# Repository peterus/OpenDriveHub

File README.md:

# OpenDriveHub

Open-source modular control platform for functional model vehicles (excavators,
dump trucks, tractors, and other ground-based RC models).

## Features

- **Modular transmitter** – plug-in front-panel slots for switches, buttons,
  potentiometers, and encoders; detected automatically at boot
- **I²C backplane** with TCA9548A multiplexer – identical standard I²C devices
  in every slot, no address conflicts, no MCU needed on modules
- **Always-on bidirectional telemetry** – battery voltage, RSSI, link state,
  and custom sensor values returned from the model
- **ESP32-based** firmware using PlatformIO + Arduino + FreeRTOS
- **Modern C++20** – `namespace odh`, `enum class`, `constexpr`, `std::optional`,
  RAII wrappers, shared libraries
- **ESP-NOW radio link** – low-latency, no router required
- **ILI9341 touch-screen display** – 320×240 colour LCD with XPT2046 resistive
  touch, LVGL widget UI for vehicle selection and live channel monitoring
- **PCA9685 servo driver** – I²C-based 16-channel PWM output on the receiver
- **Receiver-initiated discovery** – receivers broadcast their presence;
  the operator selects a vehicle on the transmitter touch screen
- **Vehicle model presets** – built-in function-to-channel maps for Generic,
  Dump Truck, Excavator, Tractor, and Crane models
- **Always-on web configuration** – WiFi AP + REST API (ESPAsyncWebServer +
  ArduinoJson v7) on both transmitter and receiver; starts automatically at
  boot, no button required; settings stored in ESP32 NVS
- **Linux simulation** – full transmitter + receiver simulation on a PC; SDL2
  display window, keyboard channel control, UDP radio loopback
- **Open hardware + firmware** under GPL-3.0

## Repository Structure

```
OpenDriveHub/
├── firmware/                   # Unified PlatformIO project (C++20, namespace odh::)
│   ├── platformio.ini          # Build config for all 5 environments
│   ├── lib/                    # Shared libraries
│   │   ├── odh-protocol/      # Packet definitions & function mapping
│   │   ├── odh-config/        # Compile-time configuration & NVS store
│   │   ├── odh-radio/         # ESP-NOW radio link (TX + RX)
│   │   ├── odh-telemetry/     # Battery monitor & telemetry data
│   │   └── odh-web/           # ESPAsyncWebServer + REST API helpers
│   ├── src/
│   │   ├── receiver/          # Receiver app (OutputManager, PCA9685, ReceiverApi)
│   │   └── transmitter/       # Transmitter app (Modules, Display, TransmitterApi)
│   ├── test/test_native/      # Native unit tests (90 tests, no hardware needed)
│   ├── data/                   # LittleFS web UI (receiver/ and transmitter/)
│   ├── include/                # LVGL & TFT_eSPI build-config headers
│   └── sim/                    # Linux simulation shims (SDL2, UDP, pthreads)
│       ├── include/            # Replacement headers (Arduino.h, esp_now.h, …)
│       └── src/                # Shim implementations
├── hardware/
│   ├── transmitter/            # Transmitter BOM and wiring reference
│   ├── receiver/               # Receiver BOM and wiring reference
│   └── modules/                # Per-module hardware documentation
│       ├── switch/
│       ├── button/
│       ├── potentiometer/
│       └── encoder/
└── docs/
    ├── index.md                # GitHub Pages one-pager
    ├── getting-started.md
    ├── architecture.md
    ├── backplane.md
    └── protocol.md
```

## Quick Start

See **[docs/getting-started.md](docs/getting-started.md)** for full build and
flash instructions.

```bash
cd firmware

# Flash transmitter
pio run -e transmitter -t upload

# Flash receiver
pio run -e receiver -t upload

# Run host-side unit tests (90 tests)
pio test -e native
```

### Run the simulation (no hardware needed)

```bash
cd firmware

# Terminal 1 – receiver
pio run -e sim_rx -t exec

# Terminal 2 – transmitter (headless terminal simulation)
pio run -e sim_tx -t exec
```

See **[firmware/sim/README.md](firmware/sim/README.md)** for full simulation docs.

## Supported Module Types

| Module | I²C Device | Channels |
|--------|------------|----------|
| Switch (toggle) | PCF8574 @ 0x20 | 8 |
| Button (momentary) | PCF8574 @ 0x21 | 8 |
| Potentiometer / fader | ADS1115 @ 0x48 | 4 |
| Encoder (absolute) | AS5600 @ 0x36 | 1 |

## Documentation

- [Getting Started](docs/getting-started.md)
- [System Architecture](docs/architecture.md)
- [Backplane & Modules](docs/backplane.md)
- [Radio Protocol](docs/protocol.md)
- [Transmitter Hardware](hardware/transmitter/README.md)
- [Receiver Hardware](hardware/receiver/README.md)
- [Simulation](firmware/sim/README.md)

## License

GPL-3.0 – see [LICENSE](LICENSE).

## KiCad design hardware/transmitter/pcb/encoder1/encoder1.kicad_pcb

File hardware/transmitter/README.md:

# Transmitter Hardware

The OpenDriveHub transmitter is a hand-held controller built around an
**ESP32** development board.

---

## Block Diagram

```
                  ┌─────────────────────┐
         I²C     │    ESP32-DevKitC     │  SPI
  ┌──────────────┤ SDA=21  SCL=22      ├────────────┐
  │              │                      │            │
  │              │ GPIO34 (ADC) ← Batt  │    ┌───────┴───────┐
  │              │                      │    │  ILI9341 LCD  │
  │              │ MOSI=23 MISO=19      │    │  320×240      │
  │              │ SCK=18  CS=5         │    │  + XPT2046    │
  │              │ DC=27   RST=26       │    │    Touch      │
  │              │ BL=32   T_CS=4       │    └───────────────┘
  │              │ T_IRQ=33             │
  │              └─────────────────────┘
  │
  ├── TCA9548A (0x70)
  │     ├── CH0 → Slot 0
  │     ├── CH1 → Slot 1
  │     ├── …
  │     └── CH5 → Slot 5
  │
  └── (pull-ups 4k7 to 3V3)
```

---

## Bill of Materials

| Qty | Component | Notes |
|-----|-----------|-------|
| 1 | ESP32-DevKitC (or equivalent) | 38-pin recommended |
| 1 | ILI9341 SPI LCD 320×240 | 2.4″ or 2.8″ breakout |
| 1 | XPT2046 resistive touch controller | Usually integrated on LCD board |
| 1 | TCA9548A I²C multiplexer breakout | Adafruit 2717 or generic |
| 2 | 4.7 kΩ resistors | I²C pull-ups on SDA / SCL |
| 1 | Voltage divider (100 kΩ + 33 kΩ) | Battery ADC on GPIO34 |
| 1 | 2S LiPo battery (7.4 V) | Optional – can be USB-powered |
| 6 | 4-pin headers / connectors | Module slot connectors |

---

## GPIO Pinout

### SPI Display (ILI9341)

| GPIO | Function |
|------|----------|
| 23 | MOSI (SDI) |
| 19 | MISO (SDO) |
| 18 | SCK |
| 5 | CS (chip select) |
| 27 | DC (data / command) |
| 26 | RST (reset) |
| 32 | Backlight (active high) |

### Touch (XPT2046)

| GPIO | Function |
|------|----------|
| 4 | T_CS (touch chip select) |
| 33 | T_IRQ (touch interrupt) |

SPI bus is shared between LCD and touch.

### I²C Bus

| GPIO | Function |
|------|----------|
| 21 | SDA |
| 22 | SCL |

All modules and the TCA9548A mux share this bus at 400 kHz.

### Battery ADC

| GPIO | Function |
|------|----------|
| 34 | Battery voltage via divider |

Divider ratio: `odh::config::kBatteryDividerRatio` (default 4.03).

---

## Programming

```bash
cd firmware
pio run -e transmitter -t upload
pio run -e transmitter -t monitor   # 115200 baud
```

---

## WiFi Configuration

The transmitter starts a WiFi AP automatically at every boot:

- **SSID:** `OpenDriveHub-Config` (configurable in `odh::config::tx::kWebApSsid`)
- **Password:** `opendrv1` (configurable in `odh::config::tx::kWebApPass`)

Open `http://192.168.4.1` in a browser to access the web UI.

REST API endpoints:
- `GET /api/status` – link state, battery, RSSI
- `GET /api/modules` – detected modules per slot
- `GET /api/mapping` – current function→channel mapping
- `POST /api/mapping` – update mapping (JSON body)

---

## Module Slot Connector

Each slot provides a **4-pin header**:

| Pin | Signal |
|-----|--------|
| 1 | 3V3 |
| 2 | GND |
| 3 | SDAn |
| 4 | SCLn |

SDAn / SCLn are the TCA9548A downstream channel pins for that slot.

---

## Enclosure Considerations

- The LCD needs a rectangular cutout of approximately 50 × 35 mm (varies by
  breakout board).
- Leave openings or slots on the sides for module headers.
- The USB port should remain accessible for firmware updates.
- A power switch between the battery and the 3V3 regulator is recommended.

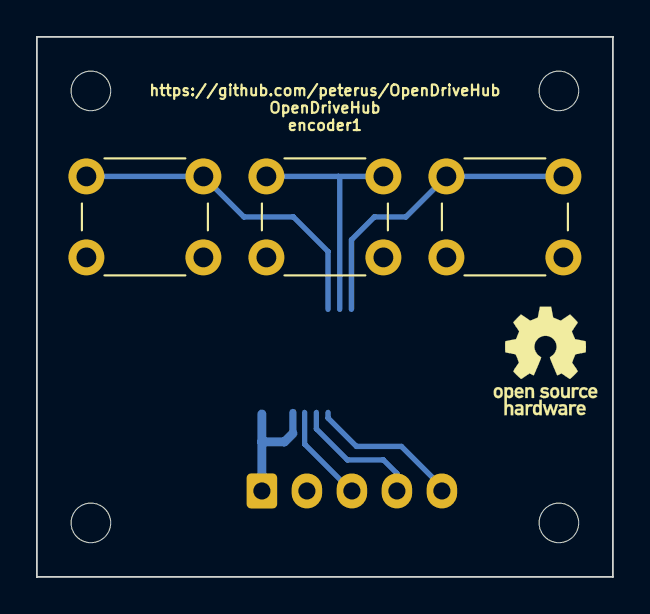
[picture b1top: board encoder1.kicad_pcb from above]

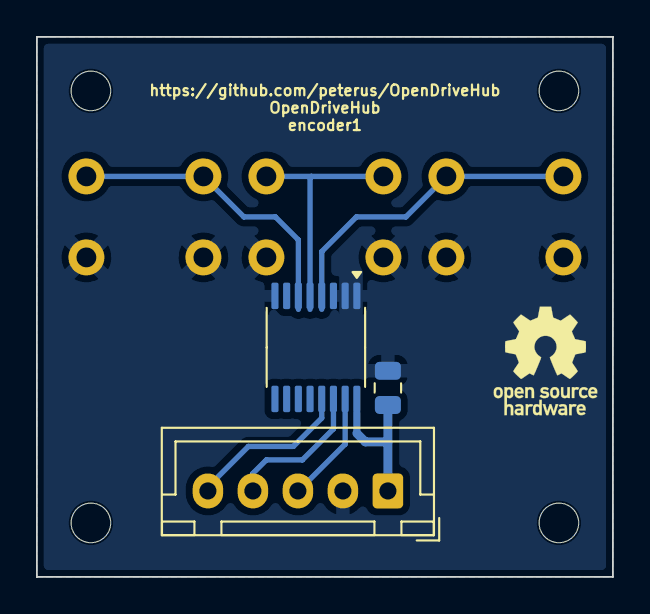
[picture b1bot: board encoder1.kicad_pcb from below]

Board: 2 copper layers, 32.0 x 30.0 mm, 12 parts (4 on the bottom side), 8 nets.

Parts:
C101: 100nF; C_0805_2012Metric
H101, H102, H103, H104: MountingHole; MountingHole_2.2mm_M2
J101: Conn_01x05; JST_XH_B5B-XH-A_1x05_P2.50mm_Vertical
LOGO101, LOGO102: Logo_Open_Hardware_Small; OSHW-Logo_5.7x6mm_SilkScreen
SW101: SW_LEFT; SW_PUSH_6mm_H5mm
SW102: SW_MID; SW_PUSH_6mm_H5mm
SW103: SW_RIGHT; SW_PUSH_6mm_H5mm
U101: PCF8574AT; TSSOP-16_4.4x5mm_P0.65mm

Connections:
+3V3: C101.1, J101.1, U101.16 (VDD)
/I2C_SCL: J101.4, U101.14 (SCL)
/I2C_SDA: J101.3, U101.15 (SDA)
/IO_INT: J101.5, U101.13 (~INT)
/NAV_LEFT: SW101.1, U101.4 (P0)
/NAV_MID: SW102.1, U101.5 (P1)
/NAV_RIGHT: SW103.1, U101.6 (P2)
GND: C101.2, J101.2, SW101.2, SW102.2, SW103.2, U101.1 (A0), U101.2 (A1), U101.3 (A2), U101.8 (GND)

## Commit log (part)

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2026-03-09 Initial commit: OpenDriveHub
2026-03-10 Update CI configuration and code to enforce cppcheck and clang-format standards
    - Adjusted cppcheck suppressions in CI configuration.
    - Added mandatory clang-format checks for all modified files.
    - Included inline cppcheck suppressions in ReceiverApi and TransmitterApi implementations.
2026-03-10 Verbessere Typen und nutze moderne C++-Funktionen in PotModule und TransmitterRadioLink
2026-03-10 Verbessere die PlattformIO-Konfiguration durch die Einführung gemeinsamer Einstellungen für native und Simulationsumgebungen
2026-03-10 Add GPL-3.0 copyright headers to all source files
    Add the standard GPL-3.0-or-later copyright and license header to all
    source files (.cpp, .h, .c), HTML files, and the sim_build.py script.
    Update copilot-instructions.md with mandatory copyright header section.
2026-03-10 Add license-headers CI job to check GPL-3.0 copyright headers
    Verifies that all source files (.cpp, .h, .c), HTML files, and Python
    scripts contain the SPDX-License-Identifier: GPL-3.0-or-later marker
    in the first 25 lines. Update copilot-instructions.md with the new job.
2026-03-10 Fix module _ready flag and add license-headers CI job
    - Add setReady() to IModule and call it in ModuleManager::scanAndInit()
    after successful begin(). Without this, modules were never marked
    ready, so inputCount() returned 0 and the web UI showed no inputs
    in the function mapping dropdowns.
    - Add license-headers CI job that checks all source, HTML, and Python
    files for the SPDX-License-Identifier: GPL-3.0-or-later marker.
2026-03-11 feat(shell): add interactive shell and console testing framework
2026-03-11 feat(ci): add console integration tests for simulation
2026-03-11 fix(shell): change ctx parameter to const in cmdModule function
2026-03-11 feat(tests): add test_filter for native unit tests
2026-03-11 feat: Implement channel management and discovery for ESP-NOW communication
    - Added WiFi channel management to the WiFi class, allowing retrieval of the current channel.
    - Updated esp_now.h to define functions for setting and getting the WiFi channel.
    - Modified sim_espnow.cpp to bind UDP sockets to channels dynamically based on the current WiFi channel.
    - Enhanced ReceiverApp and TransmitterApp to support channel discovery and migration, including callbacks for channel changes.
    - Implemented channel scanning logic to find active transmitters and manage channel acquisition.
    - Added unit tests for channel validation, discovery packet construction, and ChannelScanner functionality.
2026-03-11 Refactor receiver and transmitter commands for improved functionality and clarity
    - Updated NVS store initialization in ReceiverApi to use a more generic namespace.
    - Modified TransmitterShellCommands to enhance command help descriptions and add new commands for input and rescan functionalities.
    - Changed command syntax from "list" to "get" for channel and trim commands to align with new command structure.
    - Added new tests for config help, config reset, and model setting to ensure proper command functionality.
    - Implemented additional tests for mapping and failsafe commands to verify expected behavior.
    - Enhanced help command tests to include new commands and ensure comprehensive coverage.
2026-03-13 fix: update .gitignore to exclude Python bytecode and remove cached test files
2026-03-13 refactor: split shell command files and console tests into smaller modules
    - Extract shared helpers (shellPrintName, shellParseModel, shellListModels,
    shellListFunctions, cmdReboot) into lib/odh-shell/ShellHelpers.h/.cpp
    - Split ReceiverShellCommands.cpp into cmd_status, cmd_channel, cmd_config,
    cmd_output with ReceiverShellCmds.h internal header
    - Split TransmitterShellCommands.cpp into cmd_status, cmd_bind, cmd_channel,
    cmd_io, cmd_config with TransmitterShellCmds.h internal header
2026-03-13 Initial plan
2026-03-13 fix: correct cppcheck suppression and add missing include paths to CI
    - Change cppcheck-suppress from constParameterCallback to
    constParameterPointer in cmd_io.cpp (txCmdModule)
    - Add -I firmware/lib/odh-shell and -I firmware/lib/odh-channel
    to cppcheck CI job
2026-03-13 fix: address review comments - dangling callback ref, UDP multicast fan-out, thread-safe channel switch
2026-03-13 fix: prevent RX discovery loop by adding periodic heartbeat requests
    The receiver was stuck in a discovery loop every 3 seconds because:
    1. runChannelDiscovery()'s RAII guard clears the onDiscoveryResponse
    callback to avoid dangling stack references
    2. No DiscoveryResponse packets arrive during presence mode (the TX only
    replies to DiscoveryRequests, which are only sent during scanning)
    3. _lastTransmitterActivityMs was never updated, so checkTransmitterLoss
2026-03-13 fix: clean up DiscoveryRequest callback in TransmitterApp
2026-03-13 fix: generate unique MAC address for multiple simulation instances
2026-03-14 Fix redundant grid_w/grid_d in module_zone.scad and improve clean-all in Makefile
2026-03-15 Add OpenSCAD MCP configuration and enhance enclosure design with mounting posts and depth adjustments
2026-04-24 Restart transmitter hardware bottom-up with new OpenSCAD workflow
    - Remove hardware/transmitter/enclosure/ — flawed top-down design.
    Rebuilding from vitamins up; enclosure will come last.
    - Add openscad-hardware skill (.claude/skills/): workflow rules, BOSL2 +
    NopSCADlib cheatsheet, FDM tolerances, and pitfalls catalog.
    - Add .mcp.json registering quellant/openscad-mcp for render_perspectives,
    validate_scad, and analyze_model in the edit-check-render loop.
2026-04-24 Harden OpenSCAD feedback loop
    - Add parts/utils.scad: color palette (COLOR_METAL/PCB/PLASTIC/...),
    print_bed_check() per-part bed-fit diagnostic, explode_shift() helper.
    - Elevate render-check gate in SKILL.md to a named non-negotiable section:
    validate_scad -> analyze_model (implicit CGAL manifold check) ->
    render_perspectives -> Read PNGs. Document the MCP output_format gotcha.
    - Add BOSL2 section-view cheatsheet (back_half/left_half/bottom_half) to
2026-04-24 Add 2S LiPo battery vitamin; gitignore renders; bed to 200x200
    - parts/battery.scad: 2S LiPo 2000mAh pouch (80x35x15mm nominal),
    BOSL2-anchored with wire_exit/label_face. Includes red/black power
    leads and JST-XH 2S balance plug as visualization.
    - .gitignore: add renders/ — PNGs are regenerable via openscad-mcp
    render_perspectives, no value in tracking them.
    - Remove previously committed joystick renders (now ignored).
2026-04-24 Complete vitamin catalog: switches, encoder, buttons, display, USB-C, speaker
    - parts/toggle_switch.scad: M6-bushing long-bat toggle (13x8mm body, 51mm
    total), parametric tilt angle. Fits 2-pos, 3-pos, and momentary variants
    without geometry change.
    - parts/encoder.scad: EC11 rotary encoder with integrated push
    (12.5x13.4mm body, 37mm total), optional D-cut shaft flat.
    - parts/button_illuminated.scad: square panel-mount pushbutton with
2026-04-24 Add front-panel layout: positions all vitamins on a 280x130mm panel
    Design-brief sketch for the case shell. All vitamin positions live as
    named constants at the top of the file so they survive iteration:
    - Display centered, slightly above panel-Y center.
    - Joysticks at +/-85mm flanking the display.
    - Toggle switches in pairs of 3 in the top corners (cluster offset 102mm,
    18mm spacing) — placed outside joystick edges so the index finger
2026-04-24 Add main PCB and front-panel sub-PCBs; integrate into layout
    - parts/pcb_main.scad: main controller PCB (80x100mm) hosting ESP32-WROOM,
    charger, ADCs, I/O expanders, audio amp. 22-pin display header on the
    +Y edge so the display module plugs in directly. USB-C cutout on +X.
    JST connectors for sub-panel ribbons, joysticks, battery, speaker.
    Anchors: display_header (top of female header) and usb_c_edge.
    - parts/pcb_subpanel.scad: four bare sub-PCB variants for the front-panel
2026-04-24 Add case/ directory with first top-shell iteration
    - case/parameters.scad: case constants (WALL_T, TOP_DEPTH, CORNER_R,
    PANEL_T, screw-boss sizes) + layout positions duplicated from
    parts/layout_front.scad. Flagged with a MUST-match comment; we will
    factor out to a shared constants file if drift becomes an issue.
    - case/shell_top.scad: first top-shell geometry. Hollow rounded cuboid
    (CORNER_R=10, all edges except bottom-mating rounded), solid front
2026-04-25 Taper the top shell, add rounded vertical corners; toggle X-ray view
    - case/parameters.scad: bump CORNER_R 5->14 (rounded vertical corners on
    the front face). Add TOP_EDGE_R reference (not yet used by shell_top).
    Add TAPER_X=6 / TAPER_Y=4 — front face is 12x8 mm wider than back.
    - case/shell_top.scad: replace cuboid with prismoid for the outer shell so
    the side walls slope inward toward the back. Inner cavity follows the
    same taper to keep the wall uniform-ish. Front-face edges are still
2026-04-25 Smooth corner blend: tune TOP_EDGE_R below wall thickness
    The earlier TOP_EDGE_R=5 with CORNER_R=14 produced a visible "saddle"
    seam where the small top-edge round met the larger vertical-corner
    round at the front-top corners. Tried adding a corner_profile +
    mask3d_roundover for a spherical 3-way blend; the visual effect was
    imperceptible and bumping TOP_EDGE_R closer to CORNER_R cut through
    the front panel slab at the corners (R must stay <= WALL_T).
2026-04-25 Revert to diff()/edge_profile for top-edge rounding; document F5/F6 caveat
    prismoid's rounding2 parameter affects the *vertical* edge rounding at
    the top end (varying it from rounding1 at the bottom to rounding2 at
    the top), not the four top-face edges as I had hoped. Trying it left the
    top-face edges sharp.
    Restore the BOSL2 diff() + edge_profile([TOP]) + mask2d_roundover
    approach which actually rounds the top-face edges. It does have one
2026-04-25 Add corner_test.scad for test-printing the corner geometry
    Extracts a 55x55x35 mm chunk of the +X+Y top-shell corner so the corner
    geometry (taper + rounded vertical corner + top-edge round) can be
    validated on a small test print before committing to a full case.
    Mirrors the geometry in Z so the panel face sits flat on the bed —
    biggest flat surface for bed adhesion, walls slope inward toward the
    top so no supports are needed, and the top-edge round flows directly
2026-04-25 Add bottom shell with inverse-taper "barrel" silhouette
    bottom_shell.scad: pendant to shell_top.scad, same construction (tapered
    prismoid + diff()/edge_profile for the back-panel-edge roundover). Local
    coords place the mating face at z=0 and the back panel at z=-BOTTOM_DEPTH.
    Taper goes INVERSE to the top-shell: back-panel face is bigger than the
    mating face (matching top-shell's front panel dimensions). Result is a
    case that bulges out at both ends and is narrowest at the mating rim,
2026-04-25 Flip taper direction so the case bulges at the mating rim (real belly)
    The previous "barrel" attempt had front-panel and back-panel widest with
    the mating rim narrowest — a wasp-waist shape, the OPPOSITE of a belly.
    Both shells now taper inward from the mating rim toward their outer
    panel face. The mating rim is the widest point (CASE_W x CASE_H, 286 x
    136mm), and both panels narrow by 2*TAPER_X / 2*TAPER_Y. Side-profile
    is now a hexagonal silhouette that bulges out in the middle.
2026-04-25 Add battery cover opening + cover plate
    bottom_shell.scad: subtracts a stepped cutout from the back panel —
    a BATT_COVER_W x BATT_COVER_H recess on the exterior, plus a smaller
    BATT_OPENING_W x BATT_OPENING_H through-hole for battery insertion.
    battery_cover.scad: separate printed plate that drops into the recess.
    Sized so cover thickness (2mm) equals recess depth (2mm), giving a
    flush exterior surface; back-panel material remaining in the cover
